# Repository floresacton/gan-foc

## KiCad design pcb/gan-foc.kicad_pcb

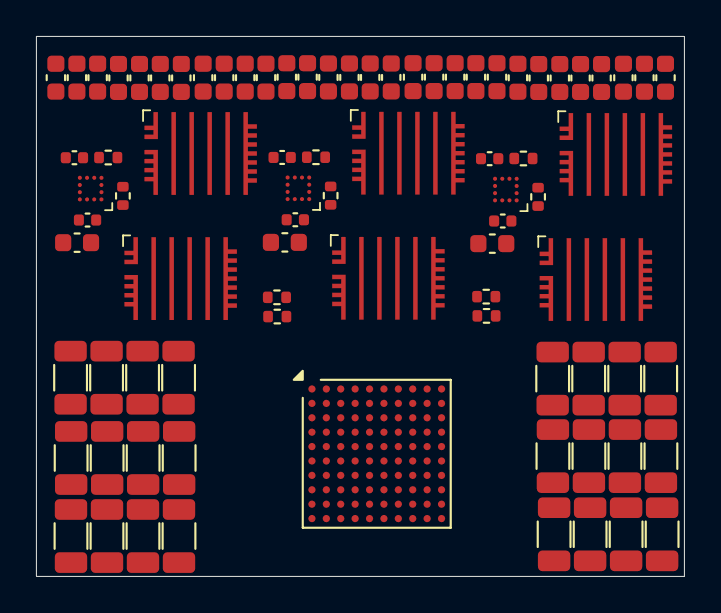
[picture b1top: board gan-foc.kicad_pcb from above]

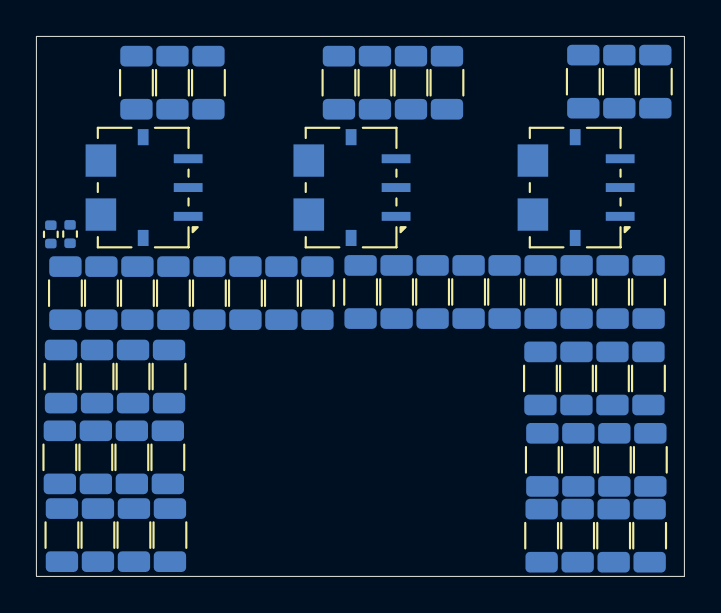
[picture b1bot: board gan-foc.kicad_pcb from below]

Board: 4 copper layers, 36.0 x 30.0 mm, 34 parts (5 on the bottom side), 25 nets, no tracks yet.

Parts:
C1, C4, C53: 10u; C_0603_1608Metric
C2, C5, C54: 100n; C_0402_1005Metric
C3, C6, C55: 220n; C_0402_1005Metric
Q1, Q2, Q3, Q4, Q21, Q22: GANE3R9
R1, R2, R5, R6, R32, R34: 10R; R_0402_1005Metric
R3, R7, R15: 10k; R_0402_1005Metric
R4, R8, R16: 1k5; R_0402_1005Metric
U1: STM32H723VGHx; TFBGA-100_8x8mm_Layout10x10_P0.8mm
U2, U3, U5: ACS781xLRTR-100B; Allegro_PSOF-7_4.8x6.4mm_P1.60mm
U4, U6, U10: LMG1205

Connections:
+5V: C1.1, C2.1, C4.1, C5.1, C53.1, C54.1, U4.A3 (VDD), U4.C4 (VDD), U6.A3 (VDD), U6.C4 (VDD), U10.A3 (VDD), U10.C4 (VDD)
/PhaseA1/CP: R3.1, R4.1
/PhaseA2/CP: R7.1, R8.1
/PhaseA/CP: R15.1, R16.1
GND: C1.2, C2.2, C4.2, C5.2, C53.2, C54.2, Q2.3 (S), Q2.4 (S), Q2.5 (S), Q2.6 (S), Q2.7 (S), Q2.9 (S), Q2.11 (S), Q2.21 (S), Q2.23 (S), Q4.3 (S), Q4.4 (S), Q4.5 (S), Q4.6 (S), Q4.7 (S), Q4.9 (S), Q4.11 (S), Q4.21 (S), Q4.23 (S), Q22.3 (S), Q22.4 (S), Q22.5 (S), Q22.6 (S), Q22.7 (S), Q22.9 (S), Q22.11 (S), Q22.21 (S), Q22.23 (S), R4.2, R8.2, R16.2, U2.2 (GND), U3.2 (GND), U4.A2 (VSS), U5.2 (GND), U6.A2 (VSS), U10.A2 (VSS)
unnamed: C3.2, Q1.3 (S), Q1.4 (S), Q1.5 (S), Q1.6 (S), Q1.7 (S), Q1.9 (S), Q1.11 (S), Q1.21 (S), Q1.23 (S), Q2.8 (D), Q2.10 (D), Q2.12 (D), Q2.13 (D), Q2.14 (D), Q2.15 (D), Q2.16 (D), Q2.17 (D), Q2.18 (D), Q2.19 (D), Q2.20 (D), Q2.22 (D), Q2.24 (D), R3.2, U4.C1 (HS), U4.D4 (HS)
unnamed: C6.2, Q3.3 (S), Q3.4 (S), Q3.5 (S), Q3.6 (S), Q3.7 (S), Q3.9 (S), Q3.11 (S), Q3.21 (S), Q3.23 (S), Q4.8 (D), Q4.10 (D), Q4.12 (D), Q4.13 (D), Q4.14 (D), Q4.15 (D), Q4.16 (D), Q4.17 (D), Q4.18 (D), Q4.19 (D), Q4.20 (D), Q4.22 (D), Q4.24 (D), R7.2, U6.C1 (HS), U6.D4 (HS)
unnamed: C55.2, Q21.3 (S), Q21.4 (S), Q21.5 (S), Q21.6 (S), Q21.7 (S), Q21.9 (S), Q21.11 (S), Q21.21 (S), Q21.23 (S), Q22.8 (D), Q22.10 (D), Q22.12 (D), Q22.13 (D), Q22.14 (D), Q22.15 (D), Q22.16 (D), Q22.17 (D), Q22.18 (D), Q22.19 (D), Q22.20 (D), Q22.22 (D), Q22.24 (D), R15.2, U10.C1 (HS), U10.D4 (HS)
unnamed: U1.C2 (VSS), U1.E4 (VSS), U1.E5 (VSS), U1.E6 (VSS), U1.J1 (VSS)
unnamed: C3.1, U4.D3 (HB)
unnamed: R1.1, U4.D2 (HOH)
unnamed: Q1.1 (G), Q1.2 (G), Q1.25 (G), R1.2, U4.D1 (HOL)
unnamed: R2.1, U4.B1 (LOH)
unnamed: Q2.1 (G), Q2.2 (G), Q2.25 (G), R2.2, U4.A1 (LOL)
unnamed: C6.1, U6.D3 (HB)
unnamed: R5.1, U6.D2 (HOH)
unnamed: Q3.1 (G), Q3.2 (G), Q3.25 (G), R5.2, U6.D1 (HOL)
unnamed: R6.1, U6.B1 (LOH)
unnamed: Q4.1 (G), Q4.2 (G), Q4.25 (G), R6.2, U6.A1 (LOL)
unnamed: C55.1, U10.D3 (HB)
unnamed: R32.1, U10.D2 (HOH)
unnamed: Q21.1 (G), Q21.2 (G), Q21.25 (G), R32.2, U10.D1 (HOL)
unnamed: R34.1, U10.B1 (LOH)
unnamed: Q22.1 (G), Q22.2 (G), Q22.25 (G), R34.2, U10.A1 (LOL)
VDD: Q1.8 (D), Q1.10 (D), Q1.12 (D), Q1.13 (D), Q1.14 (D), Q1.15 (D), Q1.16 (D), Q1.17 (D), Q1.18 (D), Q1.19 (D), Q1.20 (D), Q1.22 (D), Q1.24 (D), Q3.8 (D), Q3.10 (D), Q3.12 (D), Q3.13 (D), Q3.14 (D), Q3.15 (D), Q3.16 (D), Q3.17 (D), Q3.18 (D), Q3.19 (D), Q3.20 (D), Q3.22 (D), Q3.24 (D), Q21.8 (D), Q21.10 (D), Q21.12 (D), Q21.13 (D), Q21.14 (D), Q21.15 (D), Q21.16 (D), Q21.17 (D), Q21.18 (D), Q21.19 (D), Q21.20 (D), Q21.22 (D), Q21.24 (D)

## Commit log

2026-03-04 Save
